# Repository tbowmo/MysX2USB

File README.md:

## MysX2USB

Contains a USB MysX interface, usefull for debugging, and programming Mysensor nodes with MysX header.

Target can be supplied with power from vUSB, if jumper P2 is in place

NOTE! Using MysX 2.0 with reset pin! can be used together with MysX 1.x if
you handle reset yourself

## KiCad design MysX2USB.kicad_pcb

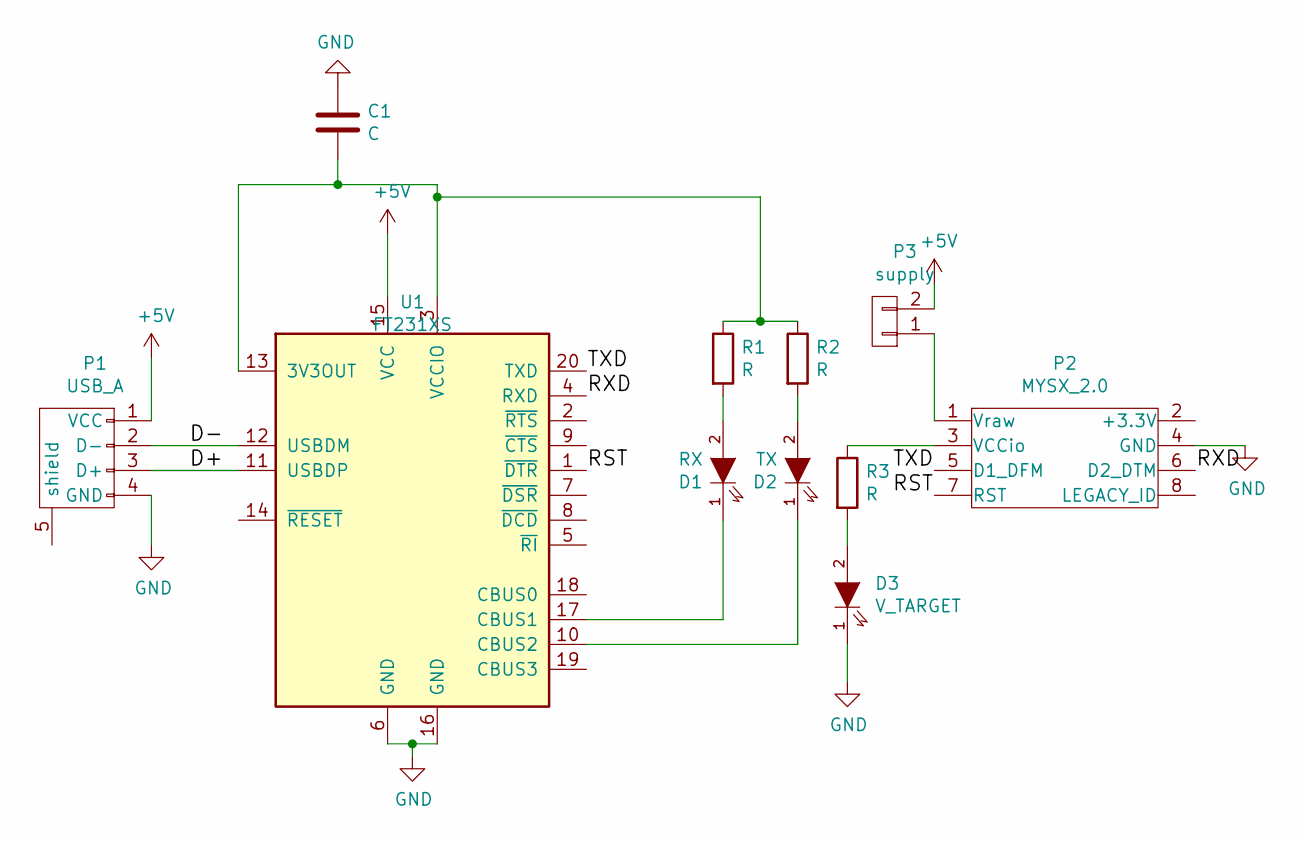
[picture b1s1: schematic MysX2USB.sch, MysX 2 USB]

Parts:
C1: C; C_0603_HandSoldering
D1: RX; LED-0603
D2: TX; LED-0603
D3: V_TARGET; LED-0603
P1: USB_A; Micro_USB
P2: MYSX_2.0; MYSX_1.0
P3: supply; Pin_Header_Straight_1x02
R1, R2, R3: R; R_0603_HandSoldering
U1: FT231XS; SSOP-20_4.4x6.5mm_Pitch0.65mm

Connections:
+5V: P1.1 (VCC), P3.2, U1.15 (VCC)
/D+: P1.3 (D+), U1.11 (USBDP)
/D-: P1.2 (D-), U1.12 (USBDM)
/RST: P2.7 (RST), U1.1 (~DTR)
/RXD: P2.6 (D2_DTM), U1.4 (RXD)
/TXD: P2.5 (D1_DFM), U1.20 (TXD)
GND: C1.1, D3.1 (K), P1.4 (GND), P1.6, P1.7, P1.8, P1.9, P2.4 (GND), U1.6 (GND), U1.16 (GND)
unnamed: C1.2, R1.1, R2.1, U1.3 (VCCIO), U1.13 (3V3OUT)
unnamed: D1.1 (K), U1.17 (CBUS1)
unnamed: D1.2 (A), R1.2
unnamed: D2.1 (K), U1.10 (CBUS2)
unnamed: D2.2 (A), R2.2
unnamed: D3.2 (A), R3.2
unnamed: P2.1 (Vraw), P3.1
unnamed: P2.3 (VCCio), R3.1

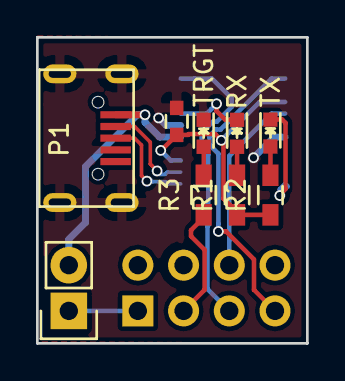
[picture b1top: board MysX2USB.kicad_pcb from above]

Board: 2 copper layers, 15.0 x 17.0 mm, 11 parts (1 on the bottom side), 15 nets.

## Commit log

2016-03-20 Updated readme and added gitignore file
2016-03-21 Changed to use MysX1.1, and made the pcb smaller. Added pdf of schematics
2016-09-10 Updated to MysX2.0
2017-02-18 Added copper pour to bottom layer
2017-02-22 Updated gerbers, preparing for pcb ordering
